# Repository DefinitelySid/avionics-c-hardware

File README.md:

# Avionics Status Indicator PCB (KiCad 10)

A 2-layer hardware status indicator board designed in **KiCad 10.0** for avionics bus debugging (e.g., ARINC 429 parity OK / bus fault telemetry on ESP32 & Arduino Uno).

## Hardware Specs
- **Layers:** 2-Layer FR-4 (F.Cu signal routing, B.Cu solid GND pour with thermal reliefs)
- **Components:** 2x 5mm THT Status LEDs, 2x 330Ω current-limiting resistors (3.3V safe), 1x 4-pin 2.54mm header
- **Verification:** Passed both ERC and DRC with 0 errors and 0 warnings

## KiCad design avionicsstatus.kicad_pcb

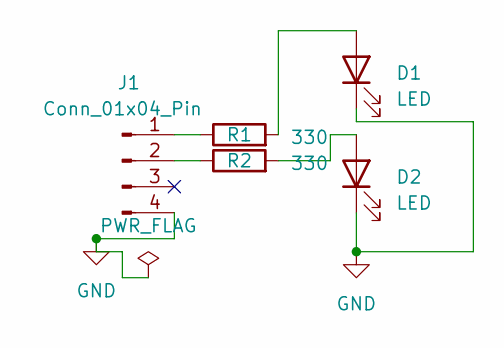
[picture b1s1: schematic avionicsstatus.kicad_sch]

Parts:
D1, D2: LED; LED_D5.0mm
J1: Conn_01x04_Pin; PinHeader_1x04_P2.54mm_Vertical
R1, R2: 330; R_Axial_DIN0207_L6.3mm_D2.5mm_P10.16mm_Horizontal

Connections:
GND: D1.1 (K), D2.1 (K), J1.4
unnamed: D1.2 (A), R1.2
unnamed: D2.2 (A), R2.2
unnamed: J1.1, R1.1
unnamed: J1.2, R2.1

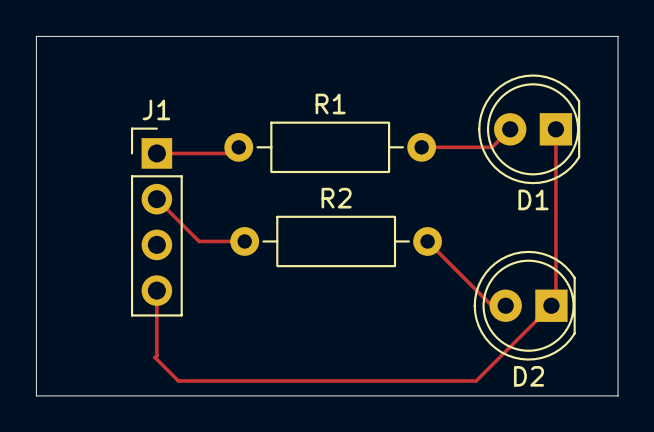
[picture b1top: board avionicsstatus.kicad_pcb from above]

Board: 2 copper layers, 32.3 x 20.0 mm, 5 parts (0 on the bottom side), 5 nets.
